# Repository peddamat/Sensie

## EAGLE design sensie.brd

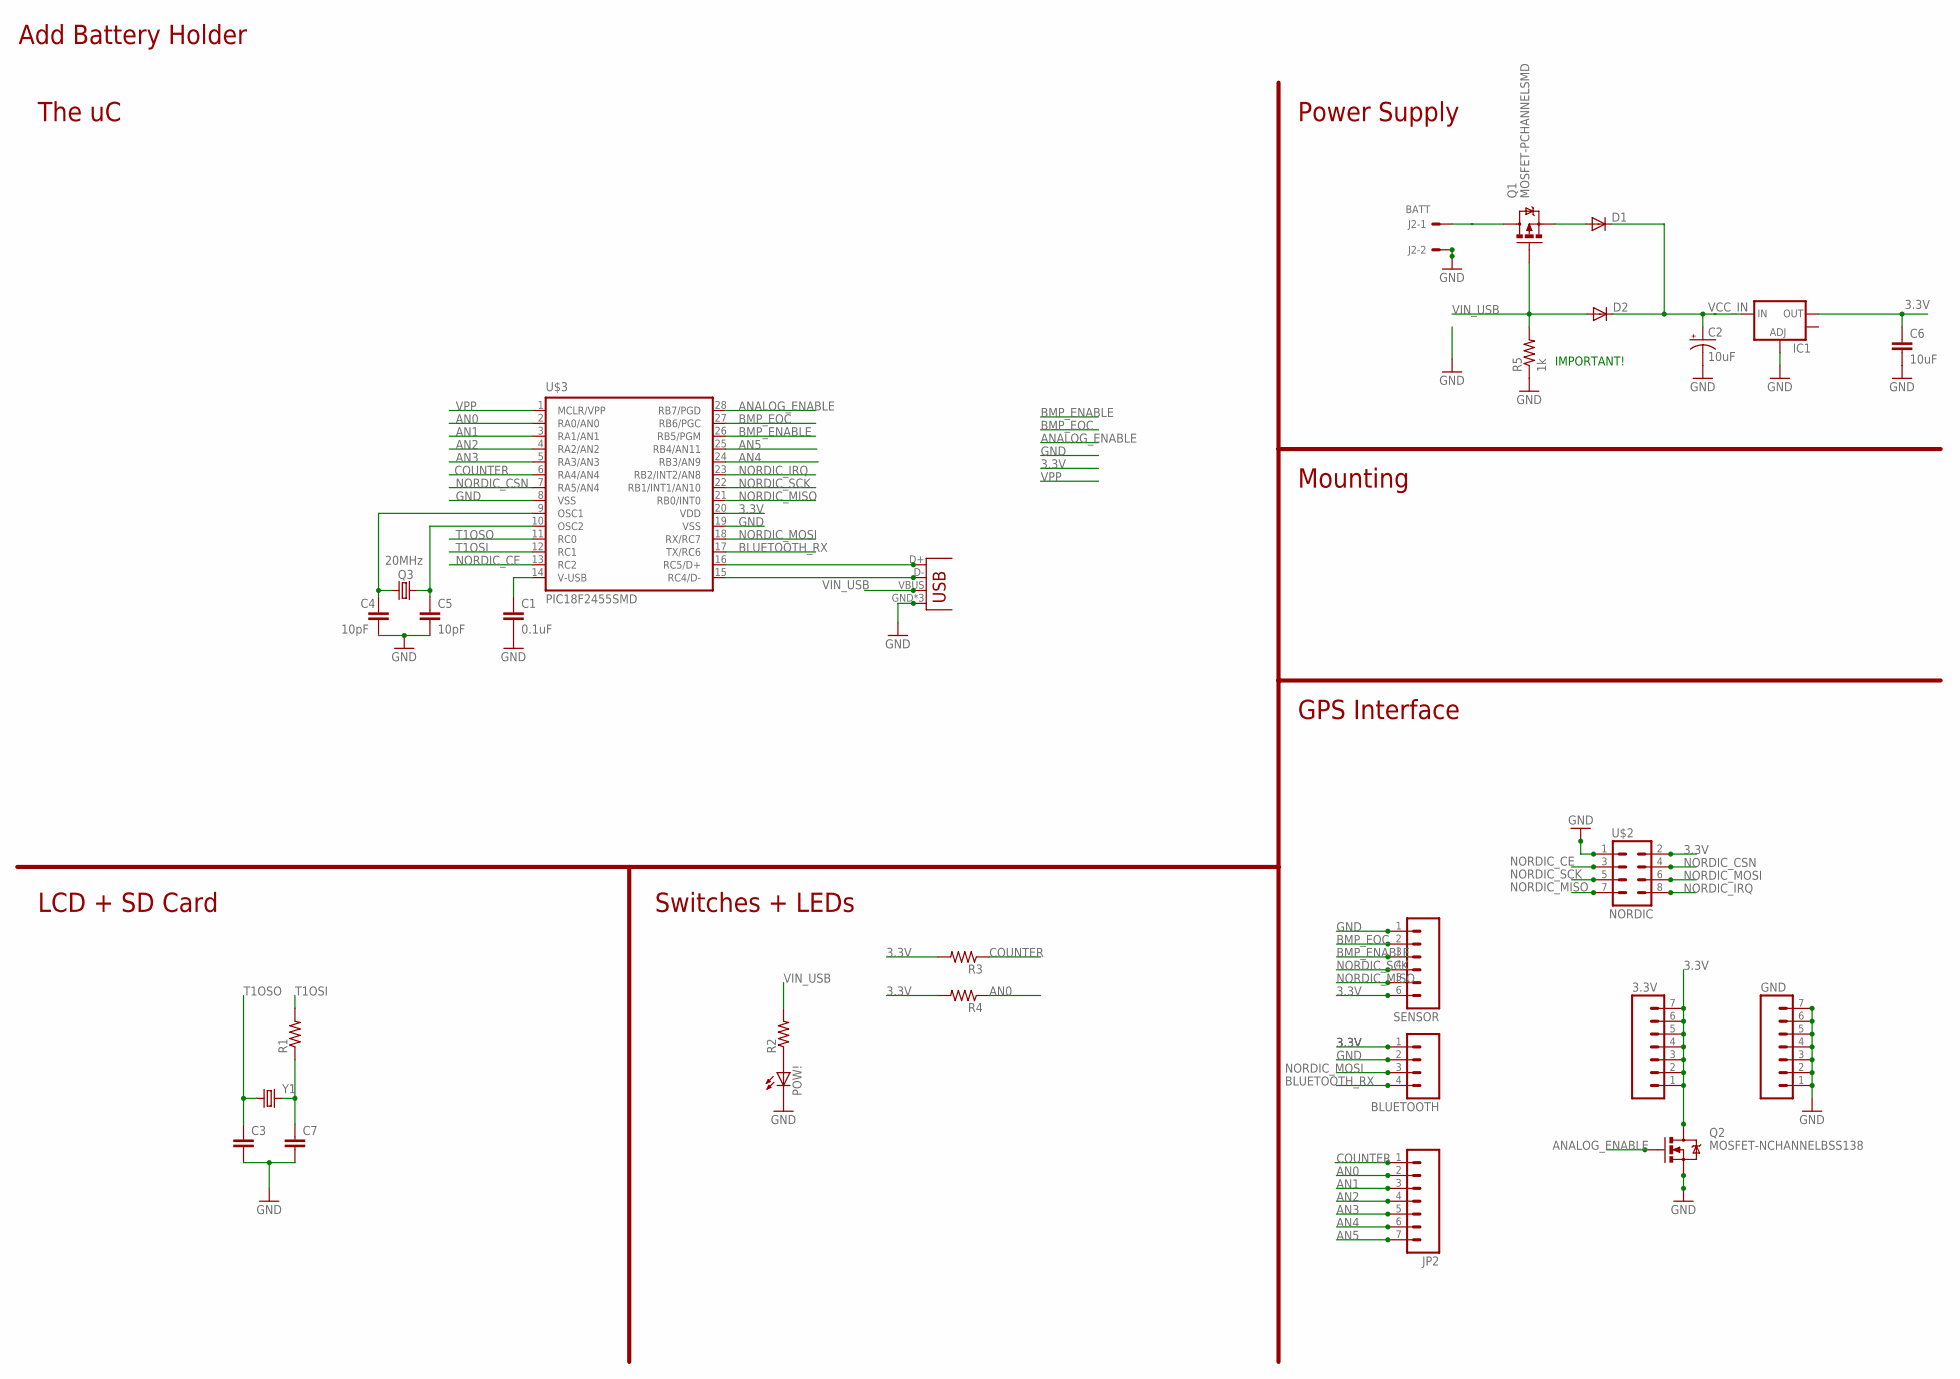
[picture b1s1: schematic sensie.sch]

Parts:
3.3V: M07; 1X07
BLUETOOTH: M04PTH; 1X04
C1: 0.1uF; 0805
C2: 10uF; EIA3528
C3, C7: CAP0603-CAP; 0603-CAP
C4, C5: 10pF; 0805
C6: 10uF; GRM43D
D1, D2: DIODESOD; SOD-323
GND: M07; 1X07
IC1: V_REG_LM1117SOT223; SOT223
J2: BATT; B2B-PH-K-S
JP2: M07; 1X07
JP3: USB-MICROB
POW!: LED0603; LED-0603
Q1: MOSFET-PCHANNELSMD; SOT23-3
Q2: MOSFET-NCHANNELBSS138; SOT23
Q3: 20MHz; HC49UP
R1, R2, R3, R4: RESISTOR0603-RES; 0603-RES
R5: 1k; 0805
SENSOR: M06SIP; 1X06
U$2: NORDIC; 2X4
U$3: PIC18F2455SMD; SO-28W
Y1: CRYSTAL32-SMD; CRYSTAL-32KHZ-SMD

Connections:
3.3V: 3.3V.1, 3.3V.2, 3.3V.3, 3.3V.4, 3.3V.5, 3.3V.6, 3.3V.7, BLUETOOTH.1, C6.A (1), IC1.2 (OUT), Q2.3 (D), R3.2, R4.2, SENSOR.6, U$2.2, U$3.20 (VDD)
AN0: JP2.2, R4.1, U$3.2 (RA0/AN0)
AN1: JP2.3, U$3.3 (RA1/AN1)
AN2: JP2.4, U$3.4 (RA2/AN2)
AN3: JP2.5, U$3.5 (RA3/AN3)
AN4: JP2.6, U$3.24 (RB3/AN9)
AN5: JP2.7, U$3.25 (RB4/AN11)
ANALOG_ENABLE: Q2.1 (G), U$3.28 (RB7/PGD)
BLUETOOTH_RX: BLUETOOTH.4, U$3.17 (TX/RC6)
BMP_ENABLE: SENSOR.3, U$3.26 (RB5/PGM)
BMP_EOC: SENSOR.2, U$3.27 (RB6/PGC)
COUNTER: JP2.1, R3.1, U$3.6 (RA4/AN4)
GND: BLUETOOTH.2, C1.2, C2.C (-), C3.2, C4.2, C5.2, C6.C (2), C7.2, GND.1, GND.2, GND.3, GND.4, GND.5, GND.6, GND.7, IC1.1 (ADJ), J2.2, JP3.GND, JP3.P$3 (GND), JP3.P$4 (GND), POW!.C, Q2.2 (S), R5.1, SENSOR.1, U$2.1, U$3.8 (VSS), U$3.19 (VSS)
unnamed: C1.1, U$3.14 (V-USB)
unnamed: POW!.A, R2.1
unnamed: C7.1, R1.1, Y1.X2 (2)
unnamed: C5.1, Q3.2, U$3.10 (OSC2)
unnamed: C4.1, Q3.1, U$3.9 (OSC1)
unnamed: JP3.D+, U$3.16 (RC5/D+)
unnamed: JP3.D-, U$3.15 (RC4/D-)
unnamed: D1.2 (A), Q1.2 (S)
NORDIC_CE: U$2.3, U$3.13 (RC2)
NORDIC_CSN: U$2.4, U$3.7 (RA5/AN4)
NORDIC_IRQ: U$2.8, U$3.23 (RB2/INT2/AN8)
NORDIC_MISO: SENSOR.5, U$2.7, U$3.21 (RB0/INT0)
NORDIC_MOSI: BLUETOOTH.3, U$2.6, U$3.18 (RX/RC7)
NORDIC_SCK: SENSOR.4, U$2.5, U$3.22 (RB1/INT1/AN10)
T1OSI: R1.2, U$3.12 (RC1)
T1OSO: C3.1, U$3.11 (RC0), Y1.X1 (1)
VCC_IN: C2.A (+), D1.1 (C), D2.1 (C), IC1.3 (IN)
VIN_BATT: J2.1, Q1.3 (D)
VIN_USB: D2.2 (A), JP3.VBUS, Q1.1 (G), R2.2, R5.2
VPP: U$3.1 (MCLR/VPP)

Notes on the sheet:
IMPORTANT!
Power Supply
GPS Interface
Add Battery Holder
Mounting
LCD + SD Card
Switches + LEDs
The uC

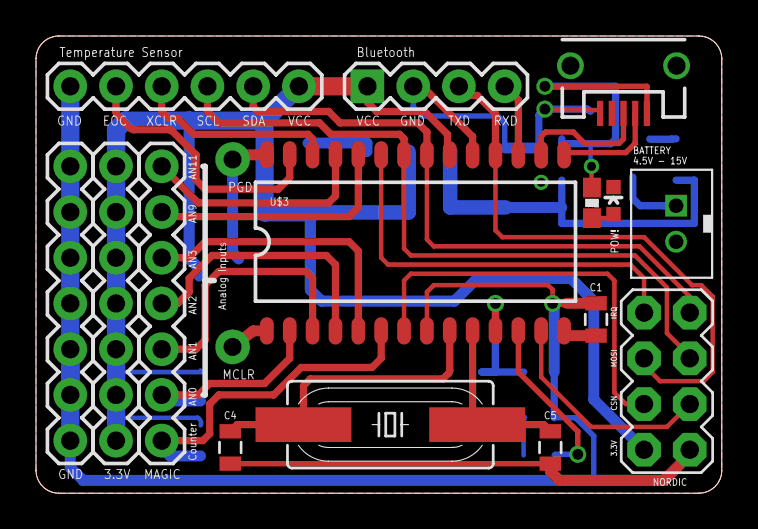
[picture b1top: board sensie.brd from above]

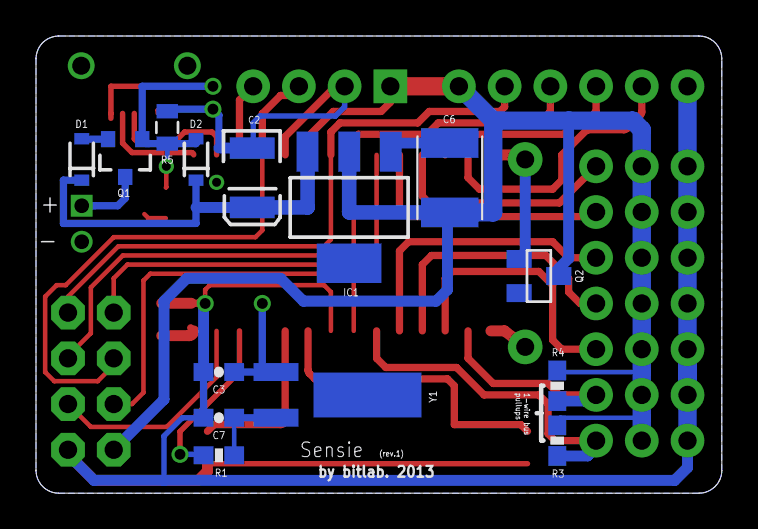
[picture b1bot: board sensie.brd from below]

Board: 2 copper layers, 38.1 x 25.4 mm, 29 parts (14 on the bottom side), 32 nets.

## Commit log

2013-06-19 Initial commit.
2013-06-19 About to refactor headers.
2013-06-19 About to refactor uC.
2013-06-19 Routing cleanup.
2013-06-19 Routing cleanup 2.
2013-06-19 Routing cleanup 3.
2013-06-19 Routing cleanup 4.
2013-06-19 About to do ground pours.
2013-06-19 Rerouting Nordic Power.
2013-06-19 Sent to OshPark.
2013-06-20 Adding documentation.

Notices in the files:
parts and their libraries:
SparkFun-Connectors: Licensing: CC v3.0 Share-Alike You are welcome to use this library for commercial purposes.
